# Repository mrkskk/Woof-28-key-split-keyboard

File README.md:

# Woof-28-key-split-keyboard

## Description

If you hate moving your entire hand to reach keys, this 28-key collumnar staggered keyboard is for you.

It lacks the inner index collumn, and the upper pinky key has been moved to an easier to reach position. 

## Photos:

## Design Inspiration:

I named it woof since it sort of looks like a dog's head.

The keyboard uses the same staggering and keyspacing as the Ferris keyboard, but the inner index collumns have been removed. 

The upper row pinky keys have been moved to a position thats easier to reach. This is inspired by the Osprette, although the upper pinky key positions aren't the same.

Links:
* [Ferris, 34-key choc spaced keyboard](https://github.com/pierrechevalier83/ferris)
* [Osprette, 34-key unibody keyboard with pinky clusters](https://github.com/smores56/osprette)

## How to Print the circuit board

1. Download the gerber.zip file
2. Send it to a PCB manufacturer of your choice.
3. Pay and wait in patience

## How to build it

### Hardware requirements

* the PCB uploaded here
* Choc switches
* Choc compatible keycaps
* MCU: any ProMicro based MCU
* Optional: Battery, TRRS switch, TRRS cable, reset switch, 

### How to install the firmware

Either:
1. Use QMK. see my keymap below
OR
2. Use ZMK and make your own shield. the ZMK keymap is yet to be made

## My keymap

[QMK keymap](https://github.com/mrkskk/qmk_firmware/tree/my_branch/keyboards/woof)

## License
It is fully Open-Sourced.

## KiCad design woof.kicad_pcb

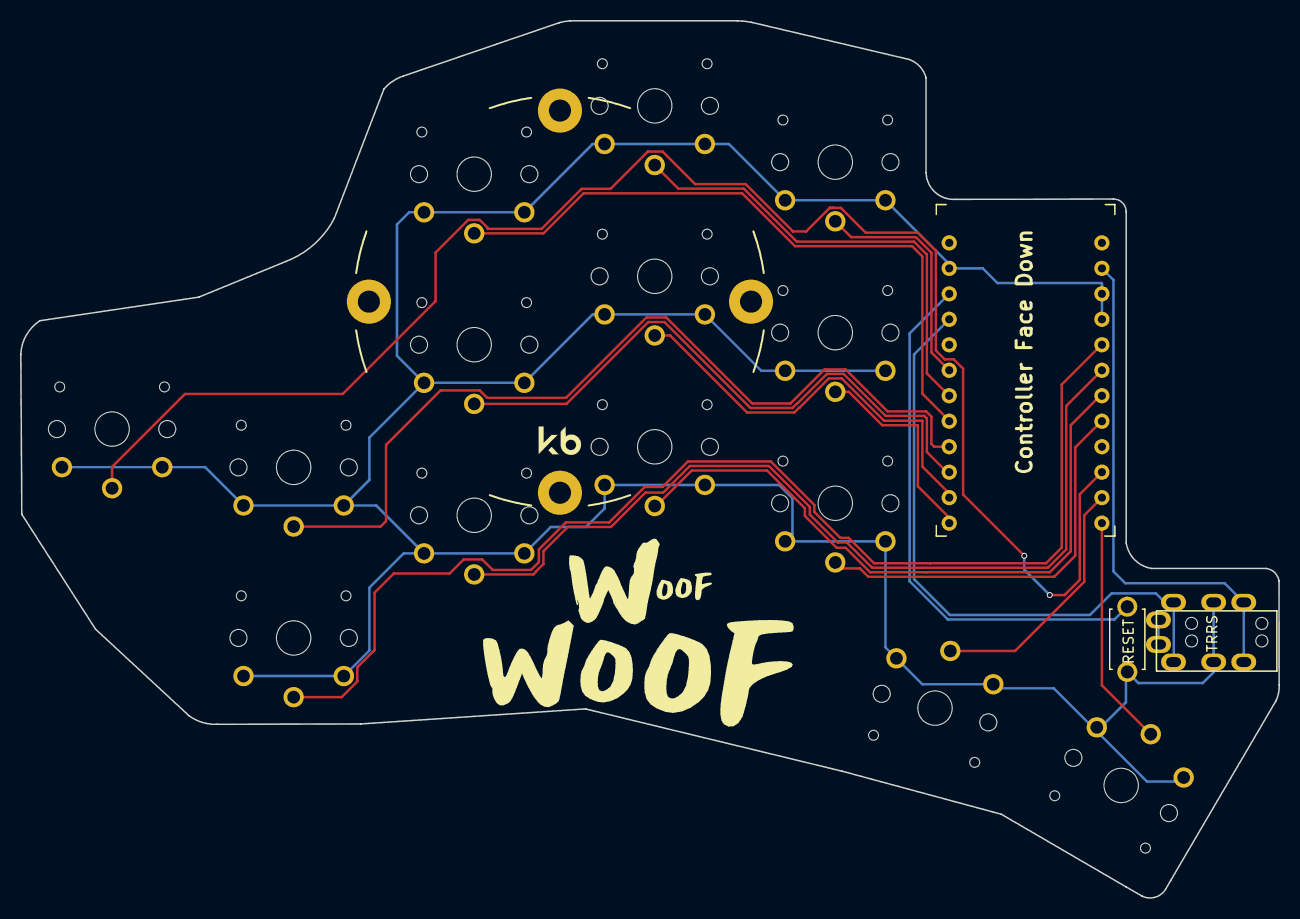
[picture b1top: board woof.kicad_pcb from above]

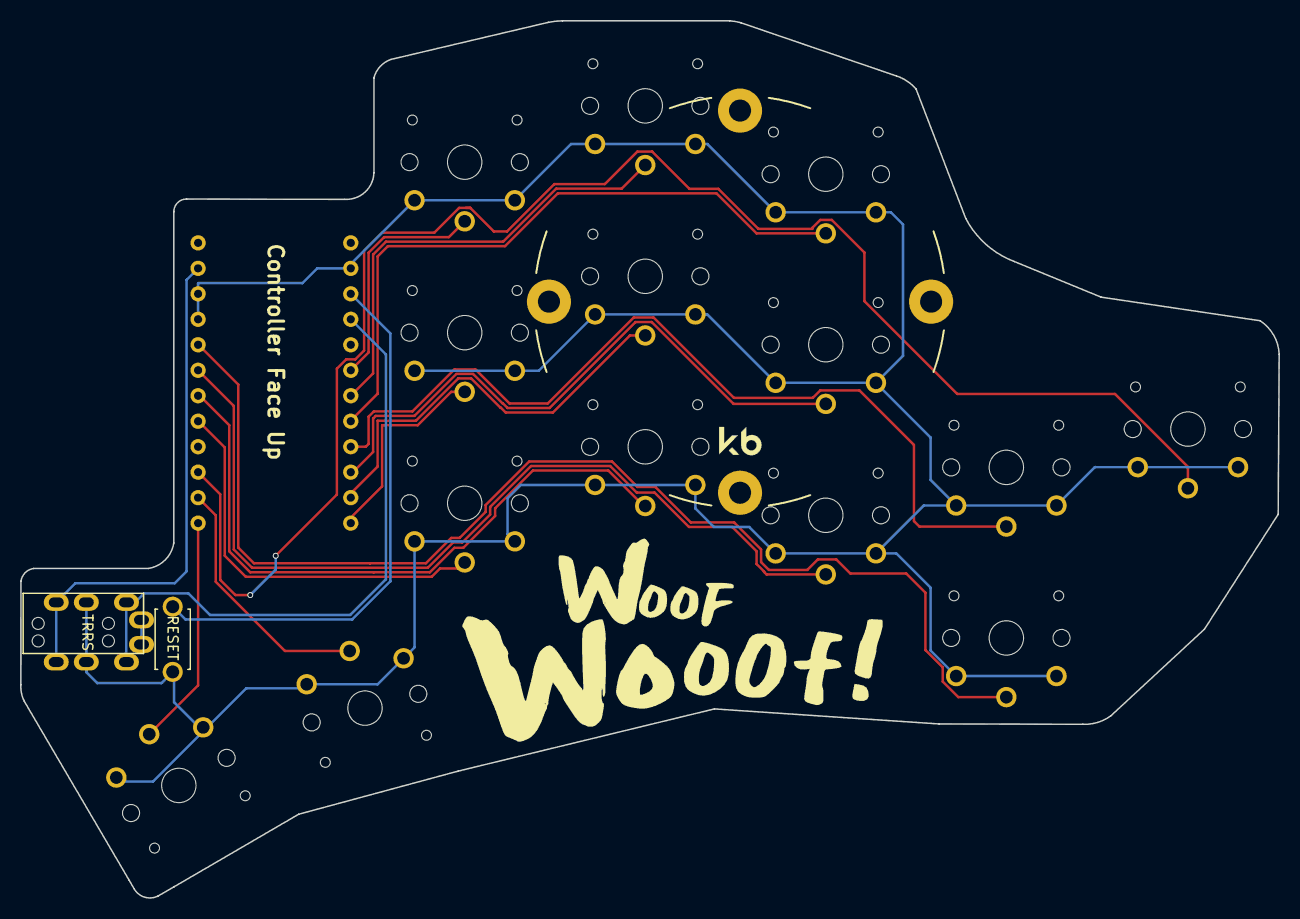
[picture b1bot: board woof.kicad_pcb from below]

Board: 2 copper layers, 125.5 x 87.4 mm, 17 parts (2 on the bottom side), 18 nets.

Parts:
J1: MJ-4PP-9
RSW1: Val**; ResetSW
SW2, SW3, SW4, SW5, SW8, SW9, SW10, SW11, SW14, SW15, SW16, SW17, SW20, SW21: SW_PUSH; SW_PG1350_reversible_b2
U1: ProMicro; ProMicro_v3

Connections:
GND: J1.C, RSW1.2, SW2.2, SW3.2, SW4.2, SW5.2, SW8.2, SW9.2, SW10.2, SW11.2, SW14.2, SW15.2, SW16.2, SW17.2, SW20.2, SW21.2, U1.3, U1.4, U1.23
unnamed: SW20.1, U1.11
unnamed: SW21.1, U1.12
unnamed: SW11.1, U1.13
unnamed: SW10.1, U1.14
SCL: SW15.1, U1.6
SDA: SW14.1, U1.5
VCC: J1.D, U1.21
col1: SW5.1, U1.19
col2: SW4.1, U1.18
col3: SW3.1, U1.17
col4: SW8.1, U1.16
col5: SW9.1, U1.15
data: J1.B, U1.2
reset: RSW1.1, U1.22
row0: SW16.1, U1.7
row1: SW17.1, U1.8
row3: SW2.1, U1.10

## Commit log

2022-05-10 Add files via upload
    PCB file.
    Edit it if you want to develop your own design inspired by this keyboard
